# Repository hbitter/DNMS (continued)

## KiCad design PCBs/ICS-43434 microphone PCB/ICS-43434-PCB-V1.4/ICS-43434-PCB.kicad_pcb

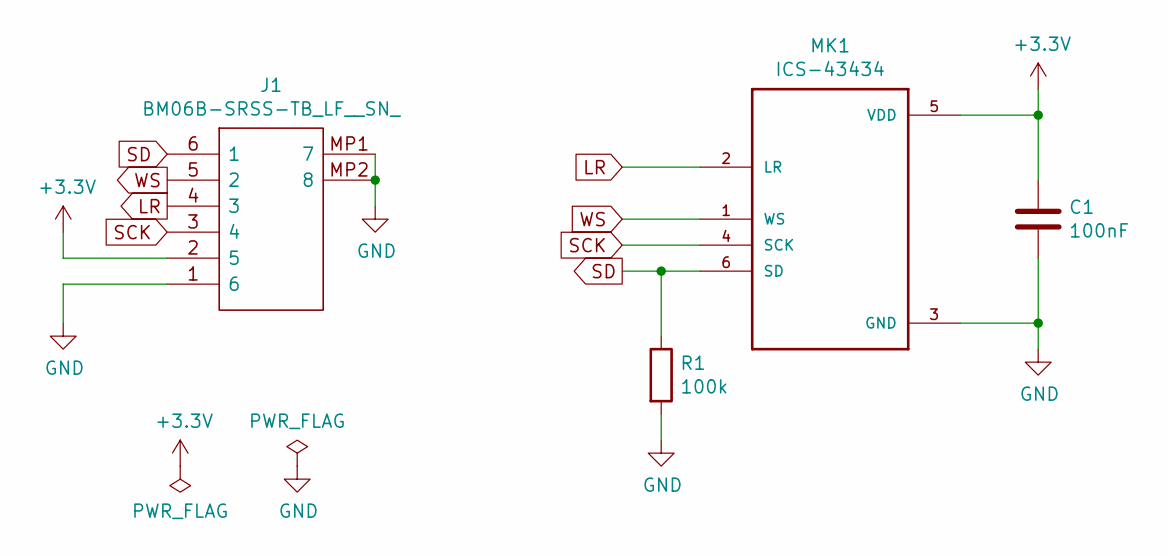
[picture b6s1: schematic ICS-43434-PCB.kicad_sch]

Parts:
C1: 100nF; C_0603_1608Metric
J1: BM06B-SRSS-TB_LF__SN_; BM06BSRSSTBLFSN; Manufacturer_Part_Number BM06B-SRSS-TB(LF)(SN)
MK1: ICS-43434; MIC_ICS-43434
R1: 100k; R_0603_1608Metric

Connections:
+3V3: C1.1, J1.2 (5), MK1.5 (VDD)
GND: C1.2, J1.1 (6), J1.MP1 (7), J1.MP2 (8), MK1.3 (GND), R1.2
LR: J1.4 (3), MK1.2 (LR)
SCK: J1.3 (4), MK1.4 (SCK)
SD: J1.6 (1), MK1.6 (SD), R1.1
WS: J1.5 (2), MK1.1 (WS)

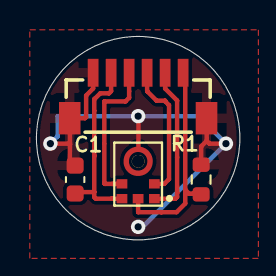
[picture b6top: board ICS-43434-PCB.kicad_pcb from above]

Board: 2 copper layers, 11.3 x 11.3 mm, 4 parts (0 on the bottom side), 6 nets.

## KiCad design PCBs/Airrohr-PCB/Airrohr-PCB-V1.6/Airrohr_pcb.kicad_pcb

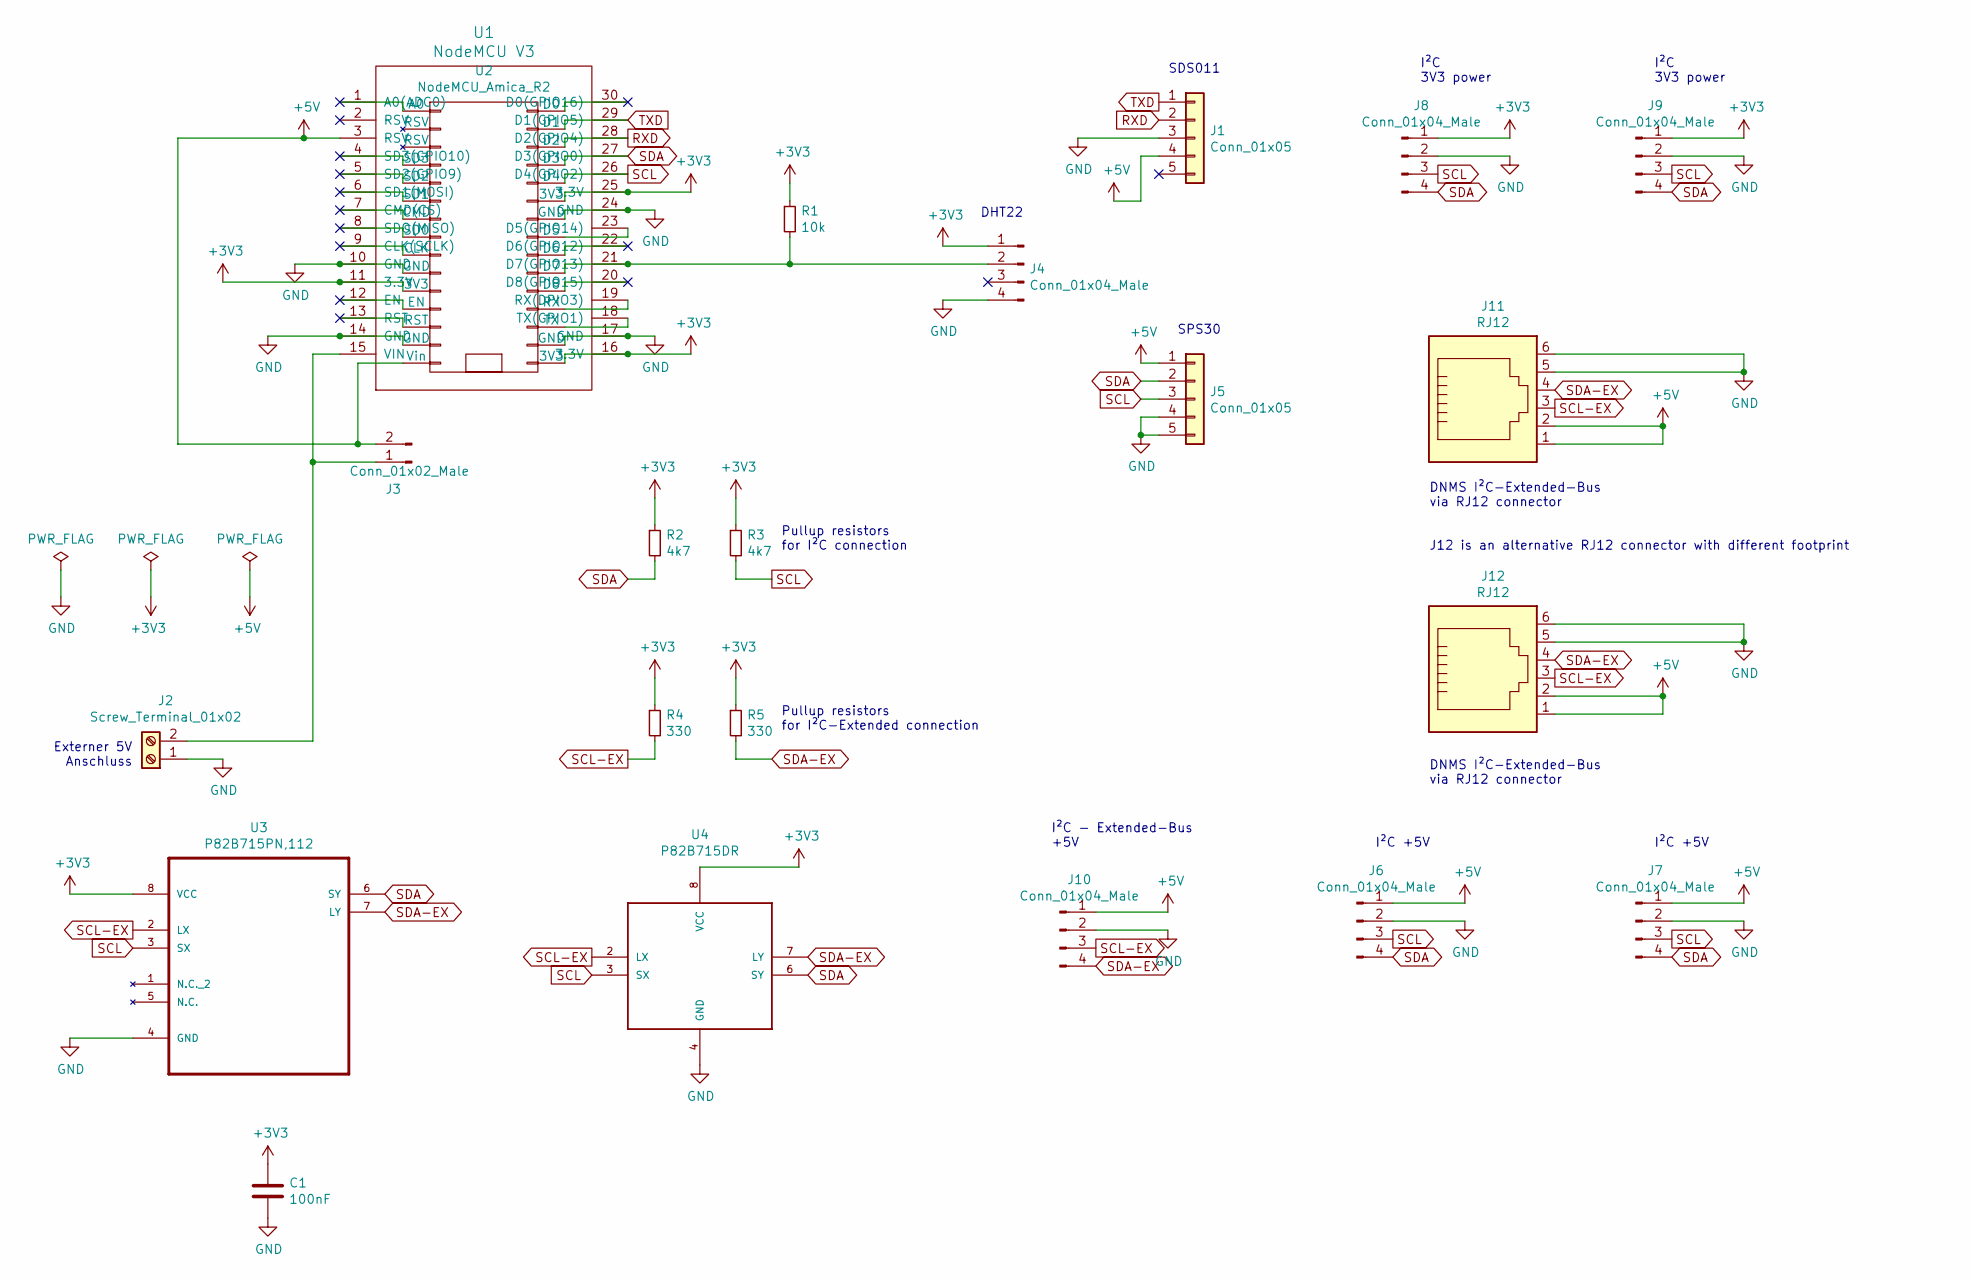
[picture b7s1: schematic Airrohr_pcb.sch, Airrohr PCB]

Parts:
C1: 100nF; C_THT_100nF_L9.0mm_W2.0mm_P5.00mm_P7.50mm
J1: Conn_01x05; JST_XH_S5B-XH-A-1_1x05_P2.50mm_Horizontal
J2: Screw_Terminal_01x02; TerminalBlock_1x02_P2,54mm_P5.08mm_Horizontal
J3: Conn_01x02_Male; PinHeader_1x02_P2.54mm_Vertical
J4, J6, J7, J8, J9, J10: Conn_01x04_Male; PinHeader_1x04_P2.54mm_Vertical
J5: Conn_01x05; JST_ZH_S5B-EH_1x05_P1.50mm_Horizontal
J11: RJ12; 54601906WPLF
J12: RJ12; E5566Q0LK22L
R1: 10k; R_Axial_DIN0207_L6.3mm_D2.5mm_P10.16mm_Horizontal
R2, R3: 4k7; R_Axial_DIN0207_L6.3mm_D2.5mm_P10.16mm_Horizontal
R4, R5: 330; R_Axial_DIN0207_L6.3mm_D2.5mm_P10.16mm_Horizontal
U1: NodeMCU V3; NodeMCU-LoLinV3
U2: NodeMCU_Amica_R2
U3: P82B715PN,112; DIP254P762X420-8
U4: P82B715DR; SOIC8

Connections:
+3V3: C1.1, J4.1, J8.1, J9.1, R1.1, R2.1, R3.1, R4.1, R5.1, U1.11 (3.3V), U1.16 (3.3V), U1.25 (3.3V), U2.11 (3V3), U2.16 (3V3), U2.25 (3V3), U3.8 (VCC), U4.8 (VCC)
+5V: J1.4, J3.2, J5.1, J6.1, J7.1, J10.1, J11.1, J11.2, J12.1, J12.2, U1.3 (RSV), U2.15 (Vin)
GND: C1.2, J1.3, J2.1, J4.4, J5.4, J5.5, J6.2, J7.2, J8.2, J9.2, J10.2, J11.5, J11.6, J12.5, J12.6, U1.10 (GND), U1.14 (GND), U1.17 (GND), U1.24 (GND), U2.10 (GND), U2.14 (GND), U2.17 (GND), U2.24 (GND), U3.4 (GND), U4.4 (GND)
unnamed: J2.2, J3.1, U1.15 (VIN)
unnamed: J4.2, R1.2, U1.21 (D7(GPIO13)), U2.21 (D7)
unnamed: U1.1 (A0(ADC0)), U2.1 (A0)
unnamed: U1.4 (SD3(GPIO10)), U2.4 (SD3)
unnamed: U1.5 (SD2(GPIO9)), U2.5 (SD2)
unnamed: U1.6 (SD1(MOSI)), U2.6 (SD1)
unnamed: U1.7 (CMD(CS)), U2.7 (CMD)
unnamed: U1.8 (SDO(MISO)), U2.8 (SD0)
unnamed: U1.9 (CLK(SCLK)), U2.9 (CLK)
unnamed: U1.12 (EN), U2.12 (EN)
unnamed: U1.13 (RST), U2.13 (RST)
unnamed: U1.18 (TX(GPIO1)), U2.18 (TX)
unnamed: U1.19 (RX(DPIO3)), U2.19 (RX)
unnamed: U1.20 (D8(GPIO15)), U2.20 (D8)
unnamed: U1.22 (D6(GPIO12)), U2.22 (D6)
unnamed: U1.23 (D5(GPIO14)), U2.23 (D5)
unnamed: U1.30 (D0(GPIO16)), U2.30 (D0)
RXD: J1.2, U1.28 (D2(GPIO4)), U2.28 (D2)
SCL: J5.3, J6.3, J7.3, J8.3, J9.3, R3.2, U1.26 (D4(GPIO2)), U2.26 (D4), U3.3 (SX), U4.3 (SX)
SCL-EX: J10.3, J11.3, J12.3, R4.2, U3.2 (LX), U4.2 (LX)
SDA: J5.2, J6.4, J7.4, J8.4, J9.4, R2.2, U1.27 (D3(GPIO0)), U2.27 (D3), U3.6 (SY), U4.6 (SY)
SDA-EX: J10.4, J11.4, J12.4, R5.2, U3.7 (LY), U4.7 (LY)
TXD: J1.1, U1.29 (D1(GPIO5)), U2.29 (D1)

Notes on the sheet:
Externer 5V Anschluss
DHT22
Pullup resistors for I²C connection
Pullup resistors for I²C-Extended connection
SPS30
I²C 3V3 power
I²C +5V
SDS011
DNMS I²C-Extended-Bus via RJ12 connector J12 is an alternative RJ12 connector with different footprint
I²C - Extended-Bus +5V
DNMS I²C-Extended-Bus via RJ12 connector

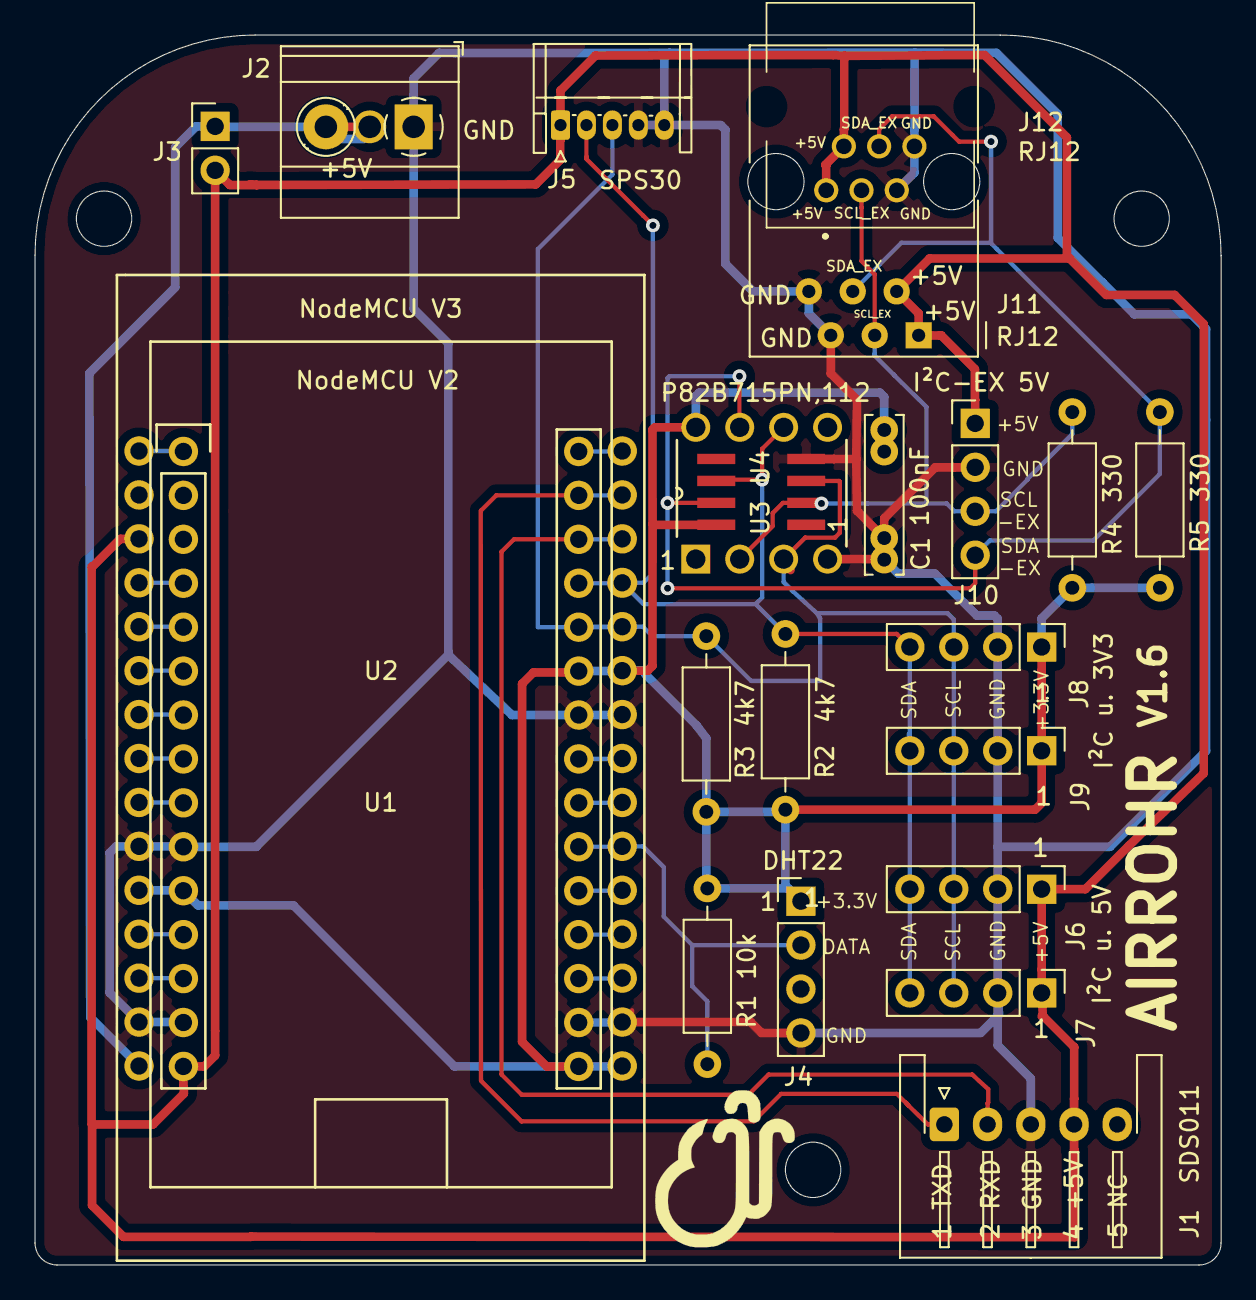
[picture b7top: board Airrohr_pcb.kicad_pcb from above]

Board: 2 copper layers, 68.6 x 71.1 mm, 22 parts (0 on the bottom side), 26 nets.

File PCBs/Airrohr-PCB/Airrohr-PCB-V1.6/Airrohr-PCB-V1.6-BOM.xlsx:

BOM | Airrohr-PCB-V1.6
Item # | Reference | Qty | Manufacturer | Manufacturer Part # | Description / Value | Package/Footprint | Type | Distributor | Distributor # | Link to Distributor | Link to alternate Source | Link to alternate Source | Notes | Price (single Qty) Mouser | Price
1 | C1 | 1 | Vishay | K104K15X7RF53H5L | Multilayer Ceramic Capacitors MLCC - Leaded 0.1uF 50volts 10% X7R 5mm LS | 5mm LS | THT | Mouser | 594-K104K15X7RF53H5 | Mouser | Reichelt | Voelkner | any other Manufacturer is ok | 0.085 | 0.085
2 | J1 | 1 | JST | S5B-XH-A | Through-hole type shrouded header, siede entry | P2,5mm | THT | Reichelt | JST XH5P ST90 | Reichelt | Voelkner | TME | (optional) | 0.2 | 0.2
3 | J2 | 1 | PTR | 50500020134G | PCB Terminal Block, Screw Terminal, 2-pole | P5,08 | THT | Voelkner | D29644 | Voelkner | Reichelt | Mouser | any other Manufacturer is ok, (optional) | 0.18 | 0.18
4 | J3 | 1 | Amphenol FCI | 10129378-902001BLF | PIN Header 1x02 P2.54mm vertical | P2.54mm | THT | Mouser | 649-1012937890201BLF | Mouser | Reichelt | Voelkner | any other Manufacturer is ok, (optional) | 0.085 | 0.085
5 | J4, J6, J7, J8, J9, J10 | 6 | A+D10:P10mphenol Commercial Products | G800W304018EU | Pin Header 2.54mm Pitch STR DIP,1x4Pin,FULL G/F,NY6T,6.1mm*2.5mm*3.0mm,Color-Bl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 | P2,54mm | THT | Mouser | 523-G800W304018EU | Mouser | Reichelt | Voelkner | any other Manufacturer is ok, (optional) | 0.085 | 0.51
6 | J5 | 1 | JST | S5B-ZR(LF)(SN) | Through-hole type shrouded header, siede entry | P1,5mm | THT | Voelkner | D19571 | Voelkner | smdv |  | (optional) | 0.53 | 0.53
7 | J11 | 1 | Amphenol FCI | 54601-906WPLF | MOD JACK RJ12 6P6C CAT 3 HORIZ. 1 PORT |  | THT | Mouser | 649-54601-906WPLF | Mouser |  |  | either J11 or J12 as alternate assembly, this is the preferred assembly because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 | 0.347 | 0.347
8 | J12 | 1 | Pulse Electronics | E5566-Q0LK22-L | Modular Jack RJ12/RJ25 6P6C SIDE ENTRY |  | THT | Mouser | 673-E5566-Q0LK22-L | Mouser | Reichelt | Voelkner | either J11 or J12 as alternate assembly, any other Manufacturer is ok, (optiona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 | 0.44 | 0.44
9 | R1 | 1 | Vishay | CCF0710K0JKE36 | Metal Film Resistor 1/4watt 10Kohms 5% Rated to 1/2watt | 6,62x2.29mm axial |  | Mouser | 71-CCF0710K0JKE36 | Mouser | Reichelt | Voelkner | any other Manufacturer is ok, Kohleschicht oder Metallschicht, 0,25Watt oder 0,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 | 0.152 | 0.152
10 | R2, R3 | 2 | Vishay | CCF074K70JKE36 | Metal Film Resistor 1/4watt 4.7Kohms 5% Rated to 1/2watt | 6,62x2.29mm axial | THT | Mouser | 71-CCF07-J-4.7K-E3 | Mouser | Reichelt | Voelkner | any other Manufacturer is ok, Kohleschicht oder Metallschicht, 0,25Watt oder 0,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 | 0.152 | 0.304
11 | R4, R5 | 2 | Vishay | CCF07330RJKE36 | Metal Film Resistor 1/4watt 330 Ohms 5% Rated to 1/2watt | 6,62x2.29mm axial |  | Mouser | 71-CCF07330RJKE36 | Mouser | Reichelt | Voelkner | any other Manufacturer is ok, Kohleschicht oder Metallschicht, 0,25Watt oder 0,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 | 0.085 | 0.17
12 | U1 | 1 | diverse | NodeMCU V3 | NodeMCU ESP8266 Entwicklungs Board V3 | 58 x 31mm | THT | KOMPUTER DE | KP06014 | KOMPUTER DE | AZ-Delivery |  | either U1 or U2 as alternate assembly | 3.12 | 3.12
13 | U2 | 1 | diverse | NodeMCU V2 | ESP8266 NodeMCU V2 Delopment Board | 48 x 26mm | THT | AZ-Delivery | NodeMCU Lua Amica Modul V2 ESP8266 ESP-12F | AZ-Delivery | BerryBase |  | either U1 or U2 as alternate assembly | 5.79 | 5.79
14 | U3 | 1 | Texas Instruments | P82B715P | Signal Buffer, Verstärker I2C Bus Extender | DIP8 | THT | Mouser | 595-P82B715P | Mouser |  |  | either U3 or U4 as alternate assembly, any other Manufacturer is ok, (optional) | 2.29 | 2.29
15 | U4 | 1 | Texas Instruments | P82B715DR | Signal Buffer, Verstärker I2C Bus Extender | SOIC8 | SMD | Mouser | 595-P82B715DR | Mouser | Reichelt |  | either U3 or U4 as alternate assembly, any other Manufacturer is ok, (optional) | 1.58 | 1.58

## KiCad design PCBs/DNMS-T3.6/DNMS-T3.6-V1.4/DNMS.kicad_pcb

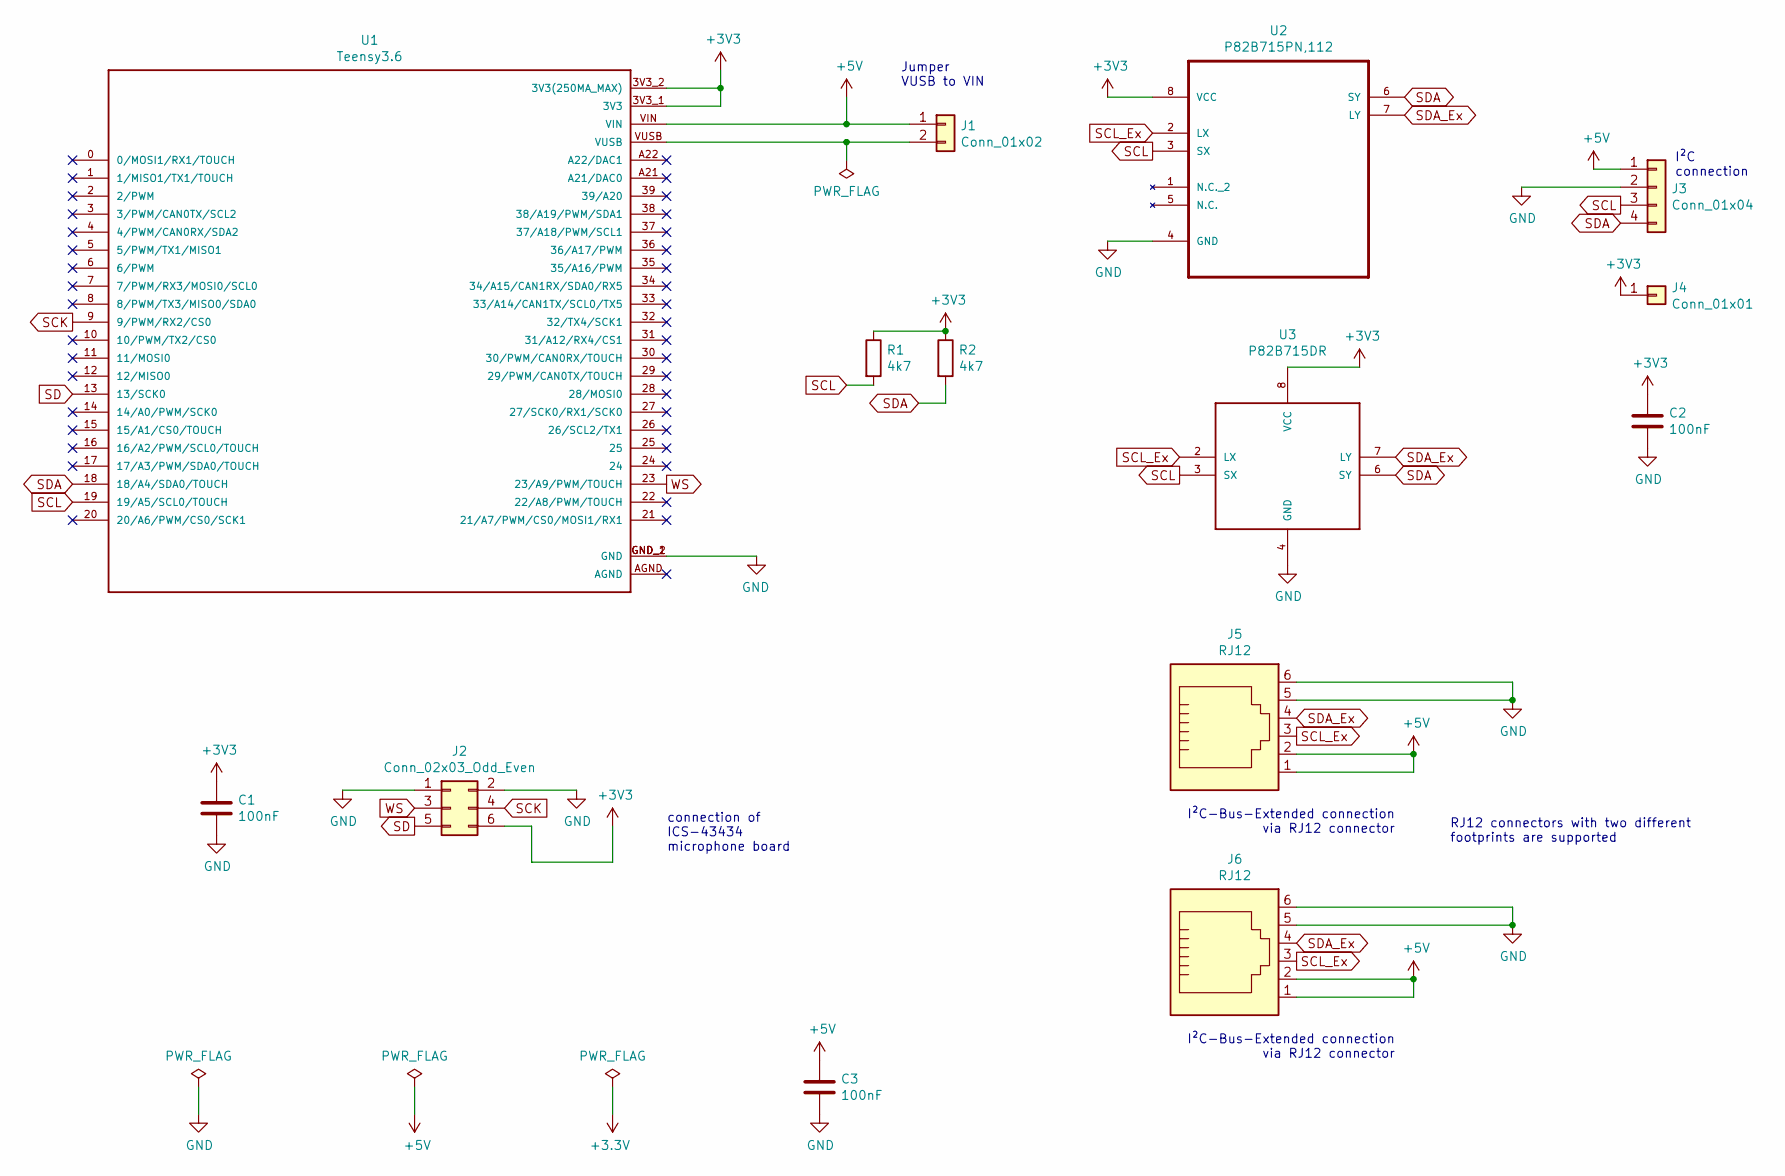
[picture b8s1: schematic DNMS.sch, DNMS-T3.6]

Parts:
C1, C2, C3: 100nF; C_THT_100nF_L9.0mm_W2.0mm_P5.00mm_P7.50mm
J1: Conn_01x02; PinHeader_1x02_P2.54mm_Vertical
J2: Conn_02x03_Odd_Even; PinHeader_2x03_P2.54mm_Vertical
J3: Conn_01x04; PinHeader_1x04_P2.54mm_Vertical
J4: Conn_01x01; PinHeader_1x01_P2.54mm_Vertical
J5: RJ12; RJ12_Amphenol_54601
J6: RJ12; RJ12_Pulse_E5566Q0LK22L
R1, R2: 4k7; R_Axial_DIN0207_L6.3mm_D2.5mm_P10.16mm_Horizontal
U1: Teensy3.6
U2: P82B715PN,112; DIP254P762X420-8
U3: P82B715DR; SOIC8

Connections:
+3V3: C1.1, C2.1, J2.6, J4.1, R1.1, R2.1, U1.3V3_1 (3V3), U1.3V3_2 (3V3(250MA_MAX)), U2.8 (VCC), U3.8 (VCC)
+5V: C3.1, J1.1, J3.1, J5.1, J5.2, J6.1, J6.2, U1.VIN
GND: C1.2, C2.2, C3.2, J2.1, J2.2, J3.2, J5.5, J5.6, J6.5, J6.6, U1.GND_1 (GND), U1.GND_2 (GND), U2.4 (GND), U3.4 (GND)
unnamed: J1.2, U1.VUSB
SCK: J2.4, U1.9 (9/PWM/RX2/CS0)
SCL: J3.3, R1.2, U1.19 (19/A5/SCL0/TOUCH), U2.3 (SX), U3.3 (SX)
SCL_Ex: J5.3, J6.3, U2.2 (LX), U3.2 (LX)
SD: J2.5, U1.13 (13/SCK0)
SDA: J3.4, R2.2, U1.18 (18/A4/SDA0/TOUCH), U2.6 (SY), U3.6 (SY)
SDA_Ex: J5.4, J6.4, U2.7 (LY), U3.7 (LY)
WS: J2.3, U1.23 (23/A9/PWM/TOUCH)

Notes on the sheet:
I²C connection
connection of ICS-43434 microphone board
I²C-Bus-Extended connection via RJ12 connector
Jumper VUSB to VIN
RJ12 connectors with two different footprints are supported

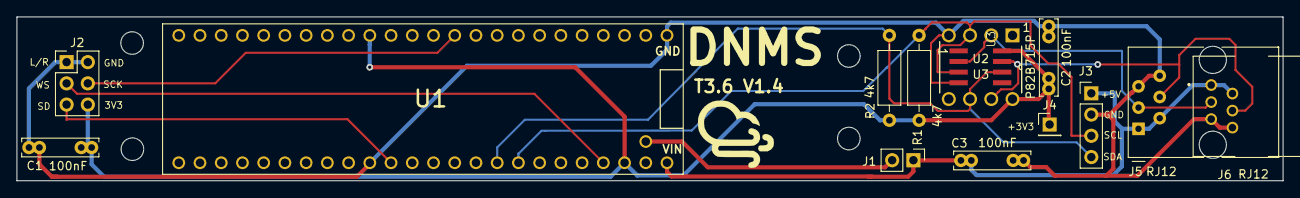
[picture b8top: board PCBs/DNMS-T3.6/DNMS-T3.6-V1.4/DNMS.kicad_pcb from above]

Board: 2 copper layers, 151.5 x 19.6 mm, 18 parts (0 on the bottom side), 11 nets.

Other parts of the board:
REF1, REF1#2, REF1#3, REF1#4: MountingHole_2.7mm_M2.5

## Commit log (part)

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2019-10-24 PCBs eingefügt
2019-10-25 Firmware eingefügt
2019-10-25 Ergänzung Readme.md
2019-10-25 README.md ergänzen
2019-10-26 README.md angepasst
2019-12-09 change of I²C library
2019-12-09 Änderung Formatierung
2019-12-09 Änderung der Formatierung
2019-12-10 new PCBs
2019-12-10 ersetzt durch V1.1.0 und V1.1.1
2019-12-10 Einfügung README.md
2019-12-10 Ergänzung der Beschreibung
2019-12-10 alte Version gelöscht
2020-03-05 Ergänzung Teensy 4.0
2020-03-05 Änderung Text
2020-05-03 1. Version Firmware für Teensy 4.0 eingefügt
2020-05-08 Austausch DNMS-T3.6-V1.2-Gerber.zip
2020-08-26 Neue PCBs
2020-08-26 Änderung Text Layout
2020-08-28 Änderungen im Bestückungsdruck/change of silkscreen
2020-09-04 Update README.md
    Small spelling correction
2020-09-04 Update DNMS.sch
    Small spelling correction
2020-09-04 spelling changes
2020-09-06 change text
2020-09-06 Text changes
2020-09-20 Update README.md
    Small spelling correction.
2020-10-04 Neues Manual (V2.0) und Stücklisten eingefügt
2020-10-04 Textänderung
2020-10-18 Manual V2.1 eingefügt, ersetzt V2.0
2020-10-23 Manual V2.2 kleine Änderungen u. Ergänzungen
2020-10-24 Textänderungen
2020-12-19 News December 2020
2021-01-31 new DNMS-T4.0+NodeMCU-V1.5
2021-01-31 Änderung von Namen
2021-02-19 Delete ZH~dd44.ffs_tmp:Zone.Identifier:$DATA
    Please delete this file / prevent upload of this file, since cloning with Windows aborts because of illegal file name:
    Cloning into 'C:\Users\[CUT]\Documents\GitHub\DNMS'...
    remote: Enumerating objects: 673, done.
    remote: Counting objects: 100% (673/673), done.
    remote: Compressing objects: 100% (384/384), done.
    remote: Total 1552 (delta 371), reused 491 (delta 283), pack-reused 879
2021-04-01 Version 2 firmware added
2021-04-01 Text for version 2 of firmware added
2021-05-30 News May 2021
2021-08-17 Replace i2c_state magic values by an enum.
2021-08-18 Add platformio confguration, hex file script
2021-09-08 Beta firmware 2.1.4 and 2.1.5 to fix I²C communication problem
2021-09-08 ICS-43434 microphone PCB - small round board
2021-09-08 Added README.md text
2021-09-10 Airrohr-ESP32_V1.1 added
2021-09-10 DNMS-RPI-HAT added
2021-09-10 README.md changed
2021-09-24 New testsoftware added
2021-12-12 Use an enum for the I2C state instead of literal numbers.
2023-01-24 New versions
2023-01-27 Corrections of bugs
2023-02-05 Wiki changes
2023-02-21 Change Readme
2023-02-22 Readme change
2023-03-15 New NodeMCU firmware
2023-03-15 Change in README.md
2023-04-04 Changed README
2023-07-20 New SW vversions, new microphone supported
2023-08-20 New Test Programms
2023-09-13 New NodeMCU firmware
    New NodeMCU firmware
2024-02-21 new firmware
2024-03-20 Change in install file and README.md for Raspberry Pi
2024-04-15 New bug fix firmware NRZ-2020-134-DNMS-5.6 for NodeMCU
2024-04-15 Changed README.md
2024-06-01 New firmware for Teensy4.0, NodeMCU and new Raspberry Pi version
2024-06-29 corretion of Raspberry Pi firmware
2024-07-01 Update News
2024-07-07 New Raspberry Pi version (0.9.18)
2024-07-28 New firmware Teensy4.0 and NodeMCU
2024-07-29 NodeMCU Version change
2024-07-29 NodeMCU firmware update images u
2024-08-23 esp-web-flasher test
2024-08-23 esp web flasher update
2024-08-23 ESP-Web-Flasher update
2024-08-23 web-flash update
2024-08-23 web flash update
2024-09-02 update web-flash
2024-09-07 update Raspberry firmware
2024-09-16 Raspberry Pi dnms-0.9.21 new version
2025-05-25 New test programs for Teensy4.0 and microphones
2026-05-17 New Teensy4.0 firmware
2026-05-18 New Teensy 4.0 firmware
2026-05-18 New Raspberry Pi firmware
2026-05-18 New Teensy 4.0 DNMS-T4.0-V1.8S Board
